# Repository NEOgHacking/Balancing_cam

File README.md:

# Balancing_cam
This is a side project to improve on the  with a new smaller esd protected pcb to prevent failures on the board, also to make the board smaller and make room for a second battery pack.
# PCB

This is a small 50x50 PCB made in kicad, it uses the esp32s3 and tmc2209 stepper drivers.
# Specs
Using:
ESP32S3 mini 1
2x TMC2209 stepper drivers
LSM6DS3 IMU
2x battery pack of 2x 18650 cells so in total 4x 18650 cells
connectivity for rc reciever and VTX

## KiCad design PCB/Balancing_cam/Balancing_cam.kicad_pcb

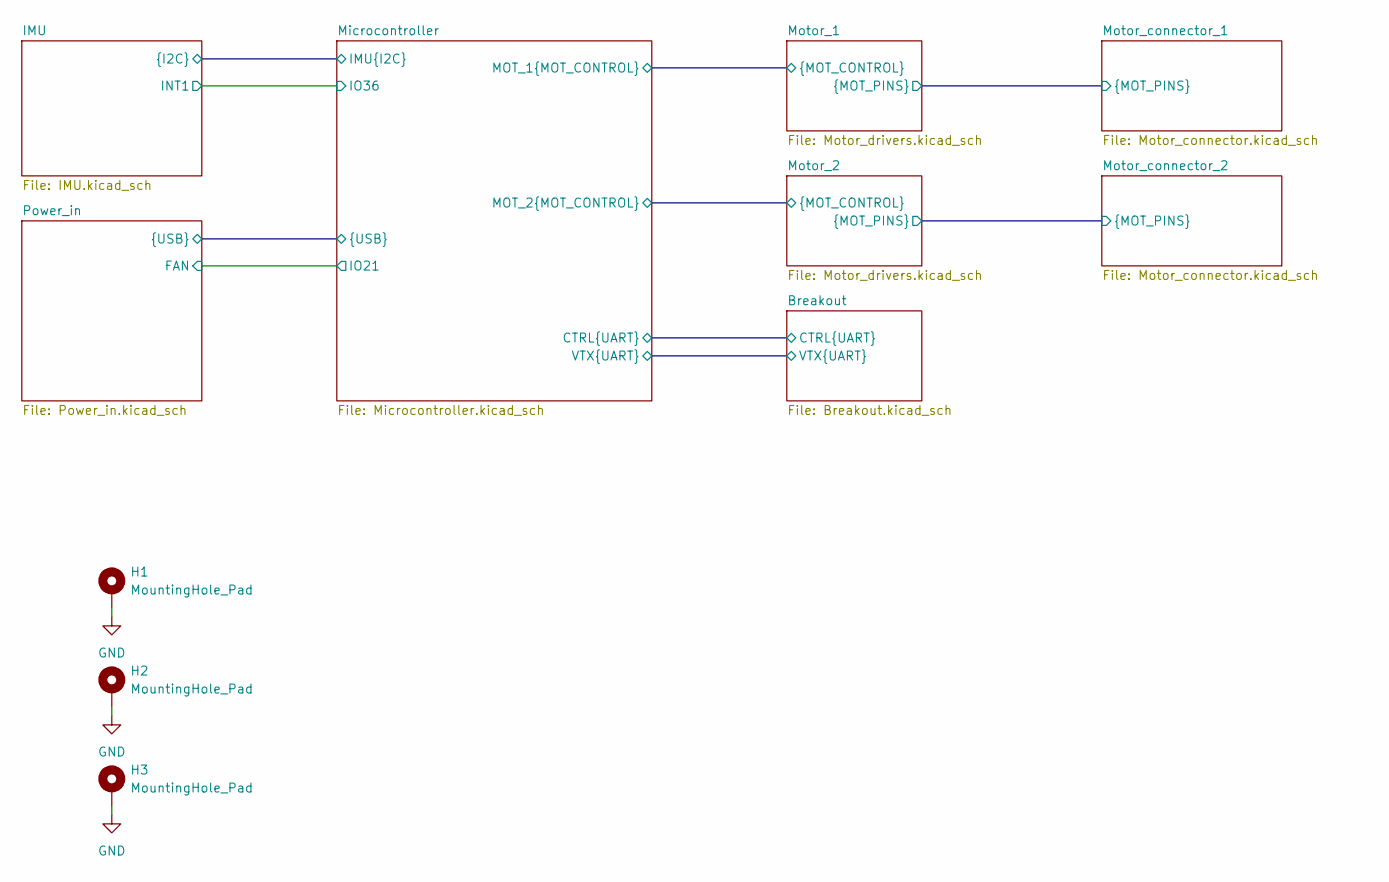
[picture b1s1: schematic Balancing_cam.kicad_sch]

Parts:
H1, H2, H3: MountingHole_Pad; MountingHole_3.2mm_M3_Pad

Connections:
GND: H1.1 (1_1), H2.1 (1_1), H3.1 (1_1); also elsewhere on the board

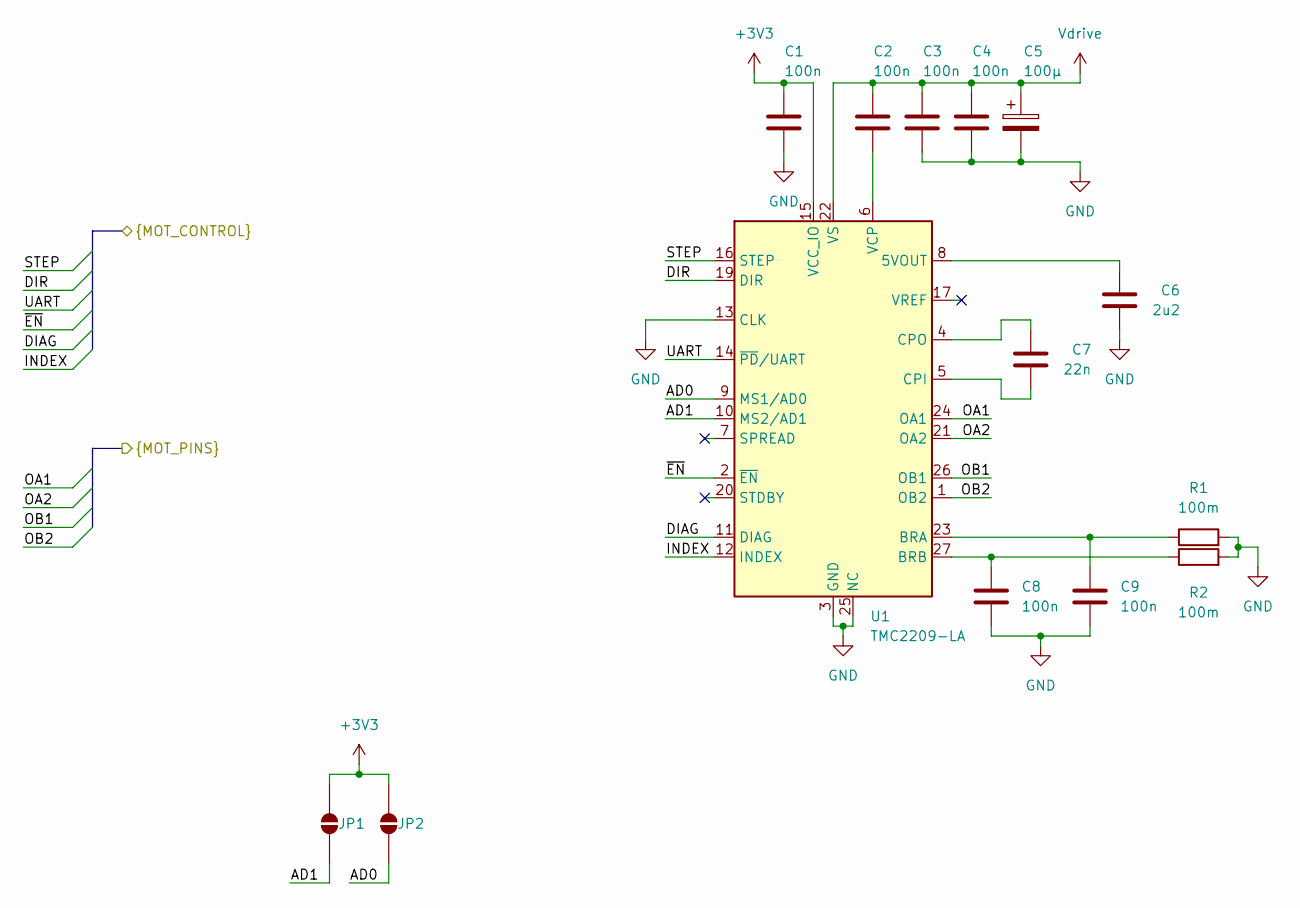
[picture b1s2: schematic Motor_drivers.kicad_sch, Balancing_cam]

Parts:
C1, C2, C3, C4, C8, C9: 100n; C_0402_1005Metric; LCSC# C307331
C5: 100μ; CP_Elec_6.3x5.4; LCSC# C2887272
C6: 2u2; C_0603_1608Metric; LCSC# C57895
C7: 22n; C_0402_1005Metric; LCSC# C337699
JP1, JP2: SolderJumper_2_Open; SolderJumper-2_P1.3mm_Open_RoundedPad1.0x1.5mm
R1, R2: 100m; R_1206_3216Metric; LCSC# C309528
U1: TMC2209-LA; VQFN-28-1EP_5x5mm_P0.5mm_EP3.7x3.7mm_ThermalVias; LCSC# C2150710

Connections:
+3V3: C1.2, JP1.1 (A), JP2.1 (A), U1.15 (VCC_IO); also elsewhere on the board
/Microcontroller/MOT_1.DIAG: U1.11 (DIAG); also elsewhere on the board
/Microcontroller/MOT_1.DIR: U1.19 (DIR); also elsewhere on the board
/Microcontroller/MOT_1.INDEX: U1.12 (INDEX); also elsewhere on the board
/Microcontroller/MOT_1.STEP: U1.16 (STEP); also elsewhere on the board
/Microcontroller/MOT_1.UART: U1.14 (~PD/UART); also elsewhere on the board
/Microcontroller/MOT_1.~EN: U1.2 (~EN); also elsewhere on the board
/Motor_1/AD0: JP2.2 (B), U1.9 (MS1/AD0)
/Motor_1/AD1: JP1.2 (B), U1.10 (MS2/AD1)
/Motor_1/OA1: U1.24 (OA1); also elsewhere on the board
/Motor_1/OA2: U1.21 (OA2); also elsewhere on the board
/Motor_1/OB1: U1.26 (OB1); also elsewhere on the board
/Motor_1/OB2: U1.1 (OB2); also elsewhere on the board
GND: C1.1, C3.1, C4.1, C5.2, C6.1, C8.2, C9.2, R1.2, R2.2, U1.3 (GND), U1.13 (CLK), U1.18 (GND), U1.25 (NC), U1.29 (GND); also elsewhere on the board
unnamed: C6.2, U1.8 (5VOUT)
unnamed: C9.1, R1.1, U1.23 (BRA)
unnamed: C8.1, R2.1, U1.27 (BRB)
unnamed: C7.1, U1.5 (CPI)
unnamed: C7.2, U1.4 (CPO)
unnamed: C2.1, U1.6 (VCP)
Vdrive: C2.2, C3.2, C4.2, C5.1, U1.22 (VS), U1.28 (VS); also elsewhere on the board

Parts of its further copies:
C10, C11, C12, C13, C17, C18: 100n; C_0402_1005Metric; LCSC# C307331
C14: 100μ; CP_Elec_6.3x5.4; LCSC# C2887272
C15: 2u2; C_0603_1608Metric; LCSC# C57895
C16: 22n; C_0402_1005Metric; LCSC# C337699
JP3, JP4: SolderJumper_2_Open; SolderJumper-2_P1.3mm_Open_RoundedPad1.0x1.5mm
R3, R4: 100m; R_1206_3216Metric; LCSC# C309528
U2: TMC2209-LA; VQFN-28-1EP_5x5mm_P0.5mm_EP3.7x3.7mm_ThermalVias; LCSC# C2150710

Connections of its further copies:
+3V3: C10.2, JP3.1 (A), JP4.1 (A), U2.15 (VCC_IO); also elsewhere on the board
/Microcontroller/MOT_1.UART: U2.14 (~PD/UART); also elsewhere on the board
/Microcontroller/MOT_2.DIAG: U2.11 (DIAG); also elsewhere on the board
/Microcontroller/MOT_2.DIR: U2.19 (DIR); also elsewhere on the board
/Microcontroller/MOT_2.INDEX: U2.12 (INDEX); also elsewhere on the board
/Microcontroller/MOT_2.STEP: U2.16 (STEP); also elsewhere on the board
/Microcontroller/MOT_2.~EN: U2.2 (~EN); also elsewhere on the board
/Motor_2/AD0: JP4.2 (B), U2.9 (MS1/AD0)
/Motor_2/AD1: JP3.2 (B), U2.10 (MS2/AD1)
/Motor_2/OA1: U2.24 (OA1); also elsewhere on the board
/Motor_2/OA2: U2.21 (OA2); also elsewhere on the board
/Motor_2/OB1: U2.26 (OB1); also elsewhere on the board
/Motor_2/OB2: U2.1 (OB2); also elsewhere on the board
GND: C10.1, C12.1, C13.1, C14.2, C15.1, C17.2, C18.2, R3.2, R4.2, U2.3 (GND), U2.13 (CLK), U2.18 (GND), U2.25 (NC), U2.29 (GND); also elsewhere on the board
unnamed: C15.2, U2.8 (5VOUT)
unnamed: C18.1, R3.1, U2.23 (BRA)
unnamed: C17.1, R4.1, U2.27 (BRB)
unnamed: C16.1, U2.5 (CPI)
unnamed: C16.2, U2.4 (CPO)
unnamed: C11.1, U2.6 (VCP)
Vdrive: C11.2, C12.2, C13.2, C14.1, U2.22 (VS), U2.28 (VS); also elsewhere on the board

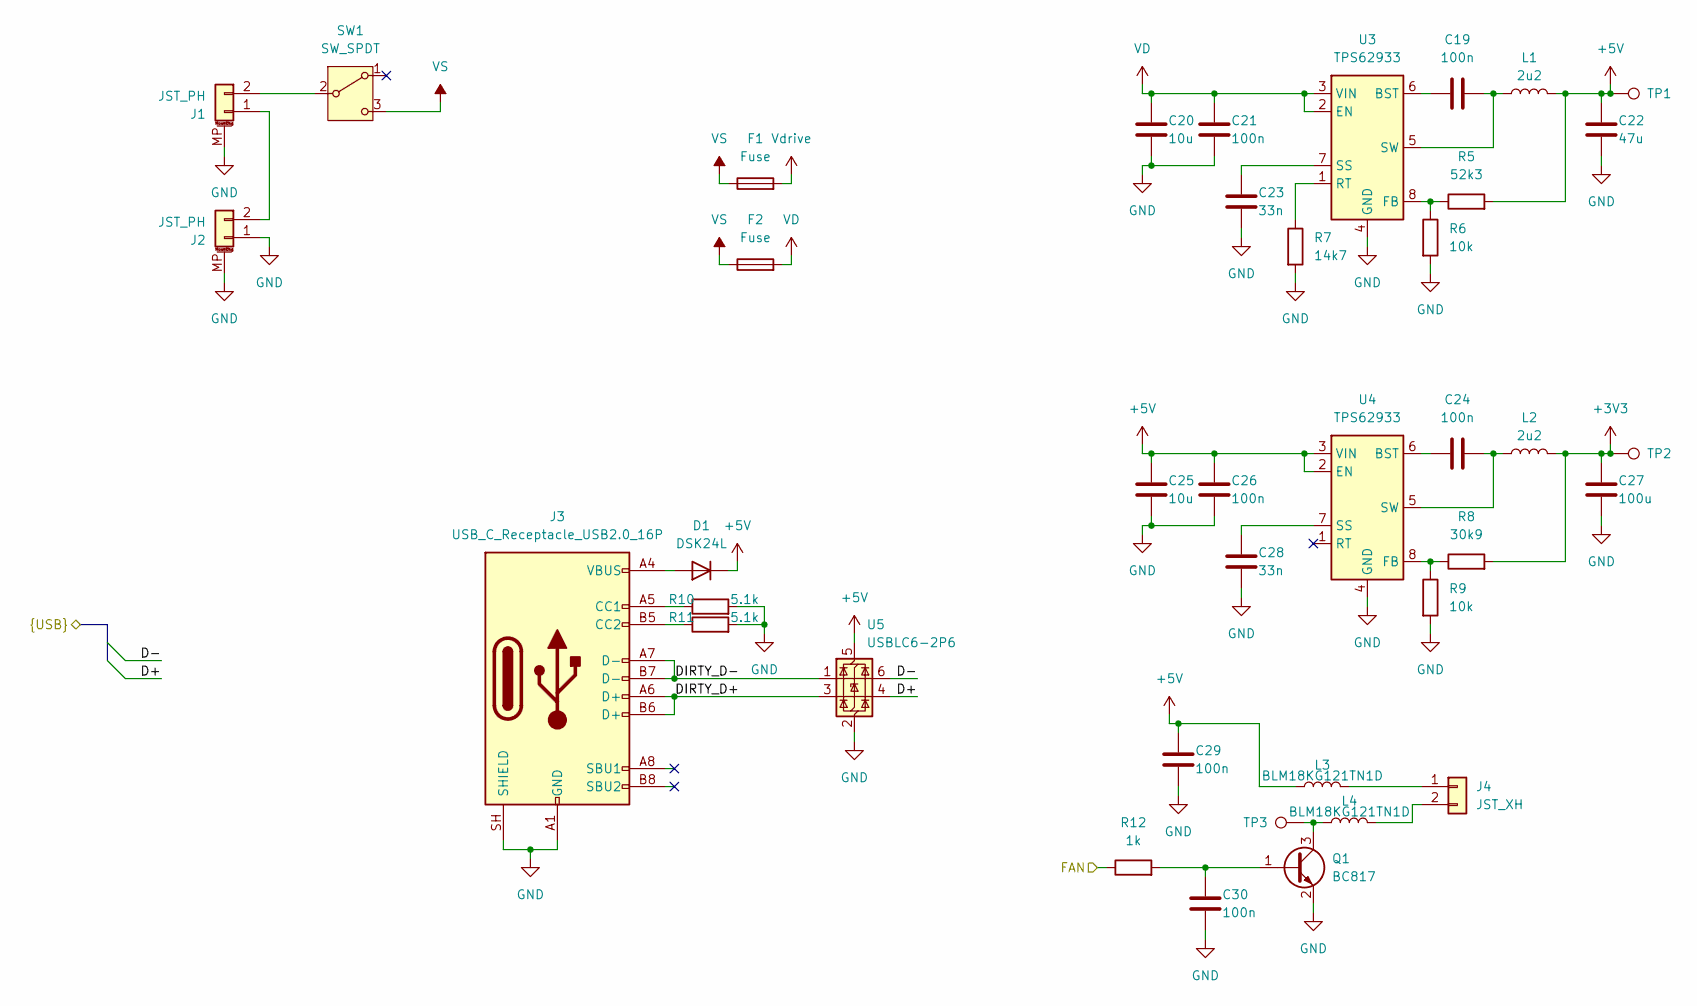
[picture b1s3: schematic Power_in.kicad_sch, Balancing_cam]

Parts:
C19, C21, C24, C26, C29, C30: 100n; C_0402_1005Metric; LCSC# C307331
C20, C25: 10u; C_0603_1608Metric; LCSC# C194427
C22: 47u; C_0805_2012Metric; LCSC# C19103846
C23, C28: 33n; C_0402_1005Metric; LCSC# C472437
C27: 100u; C_1206_3216Metric; LCSC# C380356
D1: DSK24L; D_SOD-123F; LCSC# C2939005
F1, F2: Fuse; Fuseholder_Littelfuse_Nano2_154x; LCSC# C108518
J1, J2: JST_PH; JST_PH_S2B-PH-SM4-TB_1x02-1MP_P2.00mm_Horizontal; LCSC# C295747
J3: USB_C_Receptacle_USB2.0_16P; USB_C_Receptacle_GCT_USB4105-xx-A_16P_TopMnt_Horizontal; LCSC# C165948
J4: JST_XH; JST_XH_B2B-XH-A_1x02_P2.50mm_Vertical; LCSC# C158012
L1, L2: 2u2; L_1210_3225Metric; LCSC# C3222669
L3, L4: BLM18KG121TN1D; L_0603_1608Metric; LCSC# C85831
Q1: BC817; SOT-23; LCSC# C52801
R5: 52k3; R_0402_1005Metric; LCSC# C2998086
R6, R9: 10k; R_0402_1005Metric; LCSC# C2906861
R7: 14k7; R_0402_1005Metric; LCSC# C2929988
R8: 30k9; R_0402_1005Metric; LCSC# C2933086
R10, R11: 5.1k; R_0603_1608Metric; LCSC# C105580
R12: 1k; R_0402_1005Metric; LCSC# C2906864
SW1: SW_SPDT; SS12D10G5; LCSC# C7431054
TP1, TP2, TP3: TestPoint; TestPoint_Pad_D1.5mm
U3, U4: TPS62933; SOT-583-8; LCSC# C3200405
U5: USBLC6-2P6; SOT-666; LCSC# C15999

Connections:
+3V3: C27.1, L2.2, R8.2, TP2.1 (1_1); also elsewhere on the board
+5V: C22.1, C25.1, C26.1, C29.1, D1.1 (K), L1.2, L3.1, R5.2, TP1.1 (1_1), U4.2 (EN), U4.3 (VIN), U5.5 (VBUS); also elsewhere on the board
/Microcontroller/D+: U5.4 (I/O2); also elsewhere on the board
/Microcontroller/D-: U5.6 (I/O1); also elsewhere on the board
/Microcontroller/IO21: R12.1; also elsewhere on the board
/Power_in/DIRTY_D+: J3.A6 (D+), J3.B6 (D+), U5.3 (I/O2)
/Power_in/DIRTY_D-: J3.A7 (D-), J3.B7 (D-), U5.1 (I/O1)
GND: C20.2, C21.2, C22.2, C23.2, C25.2, C26.2, C27.2, C28.2, C29.2, C30.2, J1.MP (MountPin), J2.1 (Pin_2), J2.MP (MountPin), J3.A1 (GND), J3.A12 (GND), J3.B1 (GND), J3.B12 (GND), J3.SH (SHIELD), Q1.2 (E), R6.2, R7.2, R9.2, R10.2, R11.2, U3.4 (GND), U4.4 (GND), U5.2 (GND); also elsewhere on the board
unnamed: D1.2 (A), J3.A4 (VBUS), J3.A9 (VBUS), J3.B4 (VBUS), J3.B9 (VBUS)
unnamed: J1.2 (Pin_1), SW1.2 (B)
unnamed: J1.1 (Pin_2), J2.2 (Pin_1)
unnamed: J3.A5 (CC1), R10.1
unnamed: J3.B5 (CC2), R11.1
unnamed: J4.1, L3.2
unnamed: J4.2, L4.2
unnamed: C30.1, Q1.1 (B), R12.2
unnamed: L4.1, Q1.3 (C), TP3.1 (1_1)
unnamed: C19.1, U3.6 (BST)
unnamed: R5.1, R6.1, U3.8 (FB)
unnamed: R7.1, U3.1 (RT)
unnamed: C23.1, U3.7 (SS)
unnamed: C19.2, L1.1, U3.5 (SW)
unnamed: C24.1, U4.6 (BST)
unnamed: R8.1, R9.1, U4.8 (FB)
unnamed: C28.1, U4.7 (SS)
unnamed: C24.2, L2.1, U4.5 (SW)
VD: C20.1, C21.1, F2.2, U3.2 (EN), U3.3 (VIN)
VS: F1.1, F2.1, SW1.3 (C)
Vdrive: F1.2; also elsewhere on the board

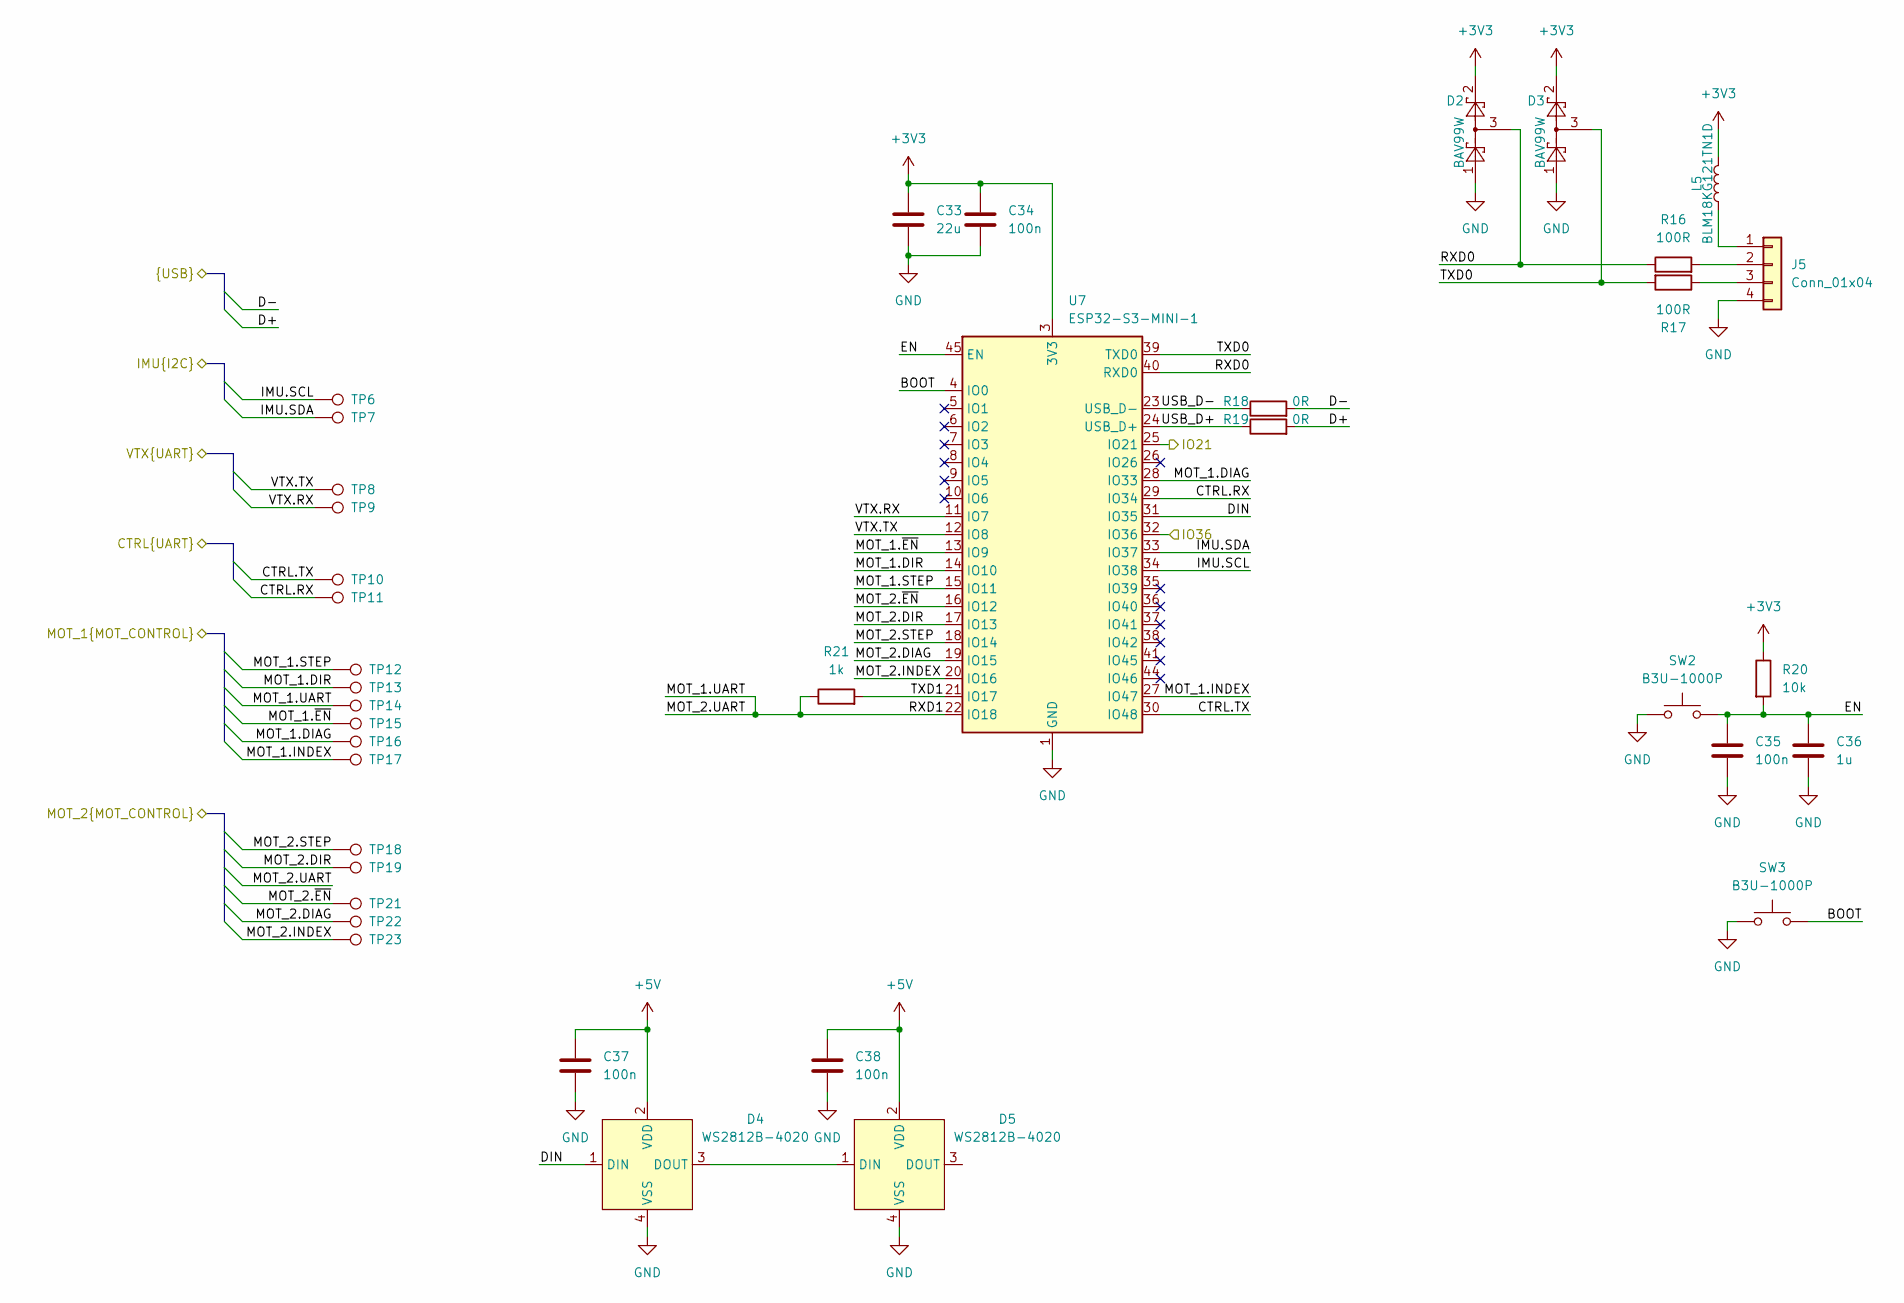
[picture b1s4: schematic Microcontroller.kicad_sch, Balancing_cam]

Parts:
C33: 22u; C_0603_1608Metric; LCSC# C59461
C34, C35, C37, C38: 100n; C_0402_1005Metric; LCSC# C307331
C36: 1u; C_0402_1005Metric; LCSC# C14445
D2, D3: BAV99W; SOT-23; LCSC# C7502727
D4, D5: WS2812B-4020; LCSC# C965557
J5: Conn_01x04; PinHeader_1x04_P2.54mm_Vertical; LCSC# C7501262
L5: BLM18KG121TN1D; L_0603_1608Metric; LCSC# C85831
R16, R17: 100R; R_0603_1608Metric; LCSC# C105588
R18, R19: 0R; R_0402_1005Metric; LCSC# C2906858
R20: 10k; R_0402_1005Metric; LCSC# C2906861
R21: 1k; R_0402_1005Metric; LCSC# C2906864
SW2, SW3: B3U-1000P; SW_SPST_B3U-1000P; LCSC# C231329
TP6, TP7, TP8, TP9, TP10, TP11, TP12, TP13, TP14, TP15, TP16, TP17, TP18, TP19, TP21, TP22, TP23: TestPoint; TestPoint_Pad_D1.5mm
U7: ESP32-S3-MINI-1; ESP32-S2-MINI-1; LCSC# C2913206

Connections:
+3V3: C33.1, C34.1, D2.2, D3.2, L5.2, R20.1, U7.3 (3V3); also elsewhere on the board
+5V: C37.1, C38.1, D4.2 (VDD), D5.2 (VDD); also elsewhere on the board
/Breakout/CTRL.RX: TP11.1 (1_1), U7.29 (IO34); also elsewhere on the board
/Breakout/CTRL.TX: TP10.1 (1_1), U7.30 (IO48); also elsewhere on the board
/Breakout/VTX.RX: TP9.1 (1_1), U7.11 (IO7); also elsewhere on the board
/Breakout/VTX.TX: TP8.1 (1_1), U7.12 (IO8); also elsewhere on the board
/IMU/INT1: U7.32 (IO36); also elsewhere on the board
/IMU/SCL: TP6.1 (1_1), U7.34 (IO38); also elsewhere on the board
/IMU/SDA: TP7.1 (1_1), U7.33 (IO37); also elsewhere on the board
/Microcontroller/BOOT: SW3.2, U7.4 (IO0)
/Microcontroller/D+: R19.2; also elsewhere on the board
/Microcontroller/D-: R18.2; also elsewhere on the board
/Microcontroller/DIN: D4.1 (DIN), U7.31 (IO35)
/Microcontroller/EN: C35.1, C36.1, R20.2, SW2.2, U7.45 (EN)
/Microcontroller/IO21: U7.25 (IO21); also elsewhere on the board
/Microcontroller/MOT_1.DIAG: TP16.1 (1_1), U7.28 (IO33); also elsewhere on the board
/Microcontroller/MOT_1.DIR: TP13.1 (1_1), U7.14 (IO10); also elsewhere on the board
/Microcontroller/MOT_1.INDEX: TP17.1 (1_1), U7.27 (IO47); also elsewhere on the board
/Microcontroller/MOT_1.STEP: TP12.1 (1_1), U7.15 (IO11); also elsewhere on the board
/Microcontroller/MOT_1.UART: R21.1, TP14.1 (1_1), U7.22 (IO18); also elsewhere on the board
/Microcontroller/MOT_1.~EN: TP15.1 (1_1), U7.13 (IO9); also elsewhere on the board
/Microcontroller/MOT_2.DIAG: TP22.1 (1_1), U7.19 (IO15); also elsewhere on the board
/Microcontroller/MOT_2.DIR: TP19.1 (1_1), U7.17 (IO13); also elsewhere on the board
/Microcontroller/MOT_2.INDEX: TP23.1 (1_1), U7.20 (IO16); also elsewhere on the board
/Microcontroller/MOT_2.STEP: TP18.1 (1_1), U7.18 (IO14); also elsewhere on the board
/Microcontroller/MOT_2.~EN: TP21.1 (1_1), U7.16 (IO12); also elsewhere on the board
/Microcontroller/RXD0: D2.3, R16.1, U7.40 (RXD0)
/Microcontroller/TXD0: D3.3, R17.2, U7.39 (TXD0)
/Microcontroller/TXD1: R21.2, U7.21 (IO17)
/Microcontroller/USB_D+: R19.1, U7.24 (USB_D+)
/Microcontroller/USB_D-: R18.1, U7.23 (USB_D-)
GND: C33.2, C34.2, C35.2, C36.2, C37.2, C38.2, D2.1, D3.1, D4.4 (VSS), D5.4 (VSS), J5.4, SW2.1, SW3.1, U7.1 (GND), U7.2 (GND), U7.42 (GND), U7.43 (GND), U7.46 (GND), U7.47 (GND), U7.48 (GND), U7.49 (GND), U7.50 (GND), U7.51 (GND), U7.52 (GND), U7.53 (GND), U7.54 (GND), U7.55 (GND), U7.56 (GND), U7.57 (GND), U7.58 (GND), U7.59 (GND), U7.60 (GND), U7.61 (GND), U7.62 (GND), U7.63 (GND), U7.64 (GND), U7.65 (GND); also elsewhere on the board
unnamed: D4.3 (DOUT), D5.1 (DIN)
unnamed: J5.1, L5.1
unnamed: J5.2, R16.2
unnamed: J5.3, R17.1

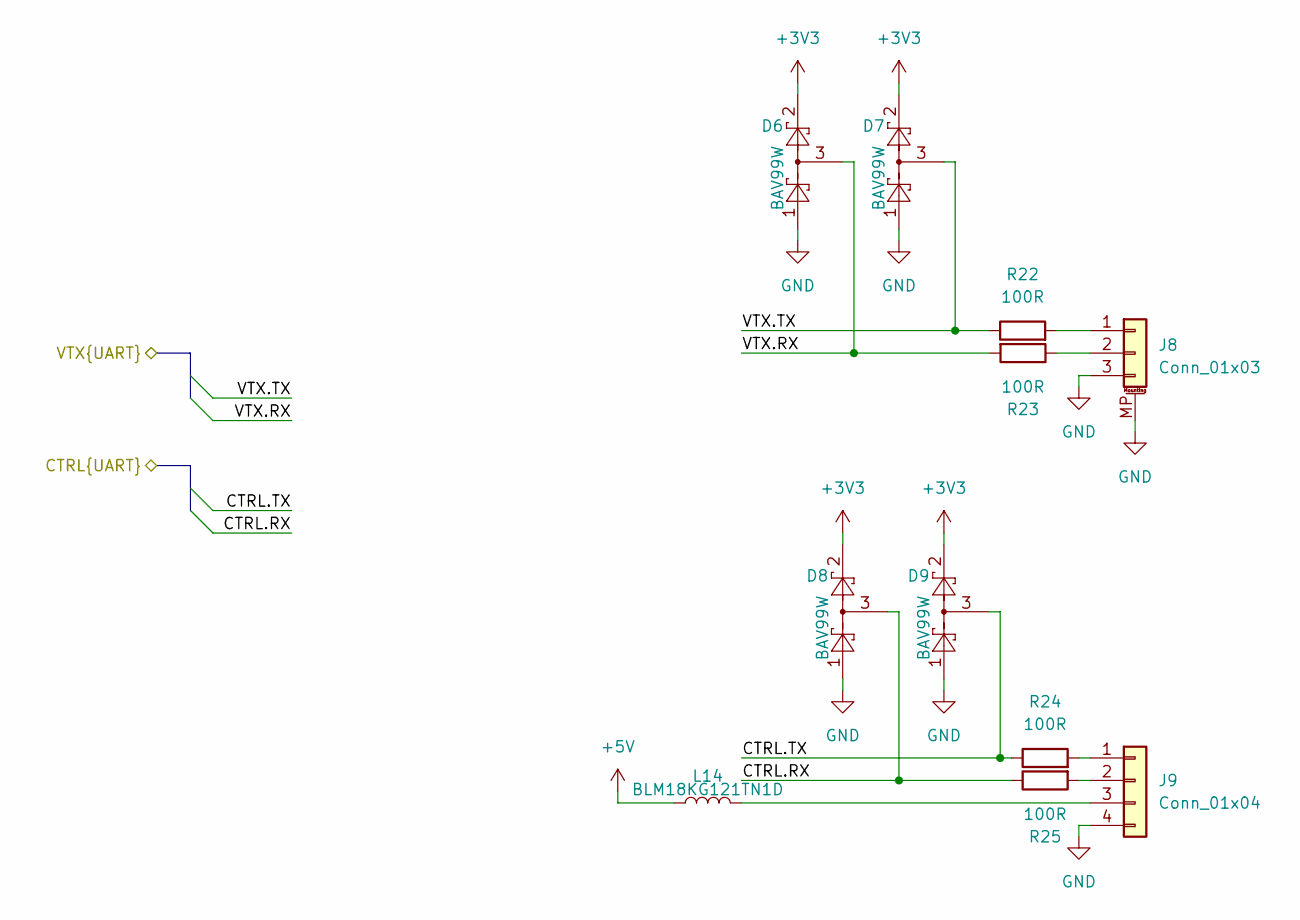
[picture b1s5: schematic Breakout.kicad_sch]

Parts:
D6, D7, D8, D9: BAV99W; SOT-23; LCSC# C7502727
J8: Conn_01x03; JST_GH_BM03B-GHS-TBT_1x03-1MP_P1.25mm_Vertical; LCSC# C160389
J9: Conn_01x04; PinHeader_1x04_P2.54mm_Vertical; LCSC# C7501262
L14: BLM18KG121TN1D; L_0603_1608Metric; LCSC# C85831
R22, R23, R24, R25: 100R; R_0603_1608Metric; LCSC# C105588

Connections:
+3V3: D6.2, D7.2, D8.2, D9.2; also elsewhere on the board
+5V: L14.1; also elsewhere on the board
/Breakout/CTRL.RX: D8.3, R25.1; also elsewhere on the board
/Breakout/CTRL.TX: D9.3, R24.1; also elsewhere on the board
/Breakout/VTX.RX: D6.3, R23.2; also elsewhere on the board
/Breakout/VTX.TX: D7.3, R22.1; also elsewhere on the board
GND: D6.1, D7.1, D8.1, D9.1, J8.3, J8.MP (MountPin), J9.4; also elsewhere on the board
unnamed: J8.1, R22.2
unnamed: J8.2, R23.1
unnamed: J9.1, R24.2
unnamed: J9.2, R25.2
unnamed: J9.3, L14.2

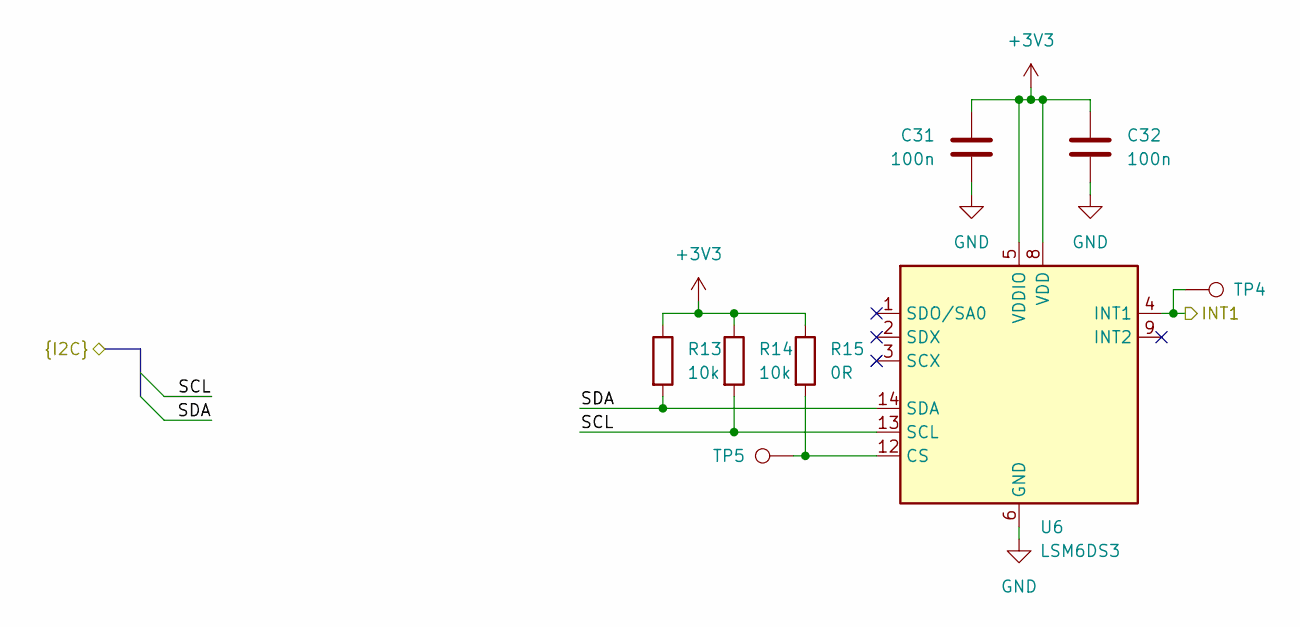
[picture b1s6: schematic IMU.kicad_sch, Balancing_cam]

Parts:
C31, C32: 100n; C_0402_1005Metric; LCSC# C307331
R13, R14: 10k; R_0402_1005Metric; LCSC# C2906861
R15: 0R; R_0402_1005Metric; LCSC# C2906858
TP4, TP5: TestPoint; TestPoint_Pad_D1.5mm
U6: LSM6DS3; LGA-14_3x2.5mm_P0.5mm_LayoutBorder3x4y; LCSC# C967633

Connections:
+3V3: C31.1, C32.1, R13.1, R14.1, R15.1, U6.5 (VDDIO), U6.8 (VDD); also elsewhere on the board
/IMU/INT1: TP4.1 (1_1), U6.4 (INT1); also elsewhere on the board
/IMU/SCL: R14.2, U6.13 (SCL); also elsewhere on the board
/IMU/SDA: R13.2, U6.14 (SDA); also elsewhere on the board
GND: C31.2, C32.2, U6.6 (GND), U6.7 (GND); also elsewhere on the board
unnamed: R15.2, TP5.1 (1_1), U6.12 (CS)

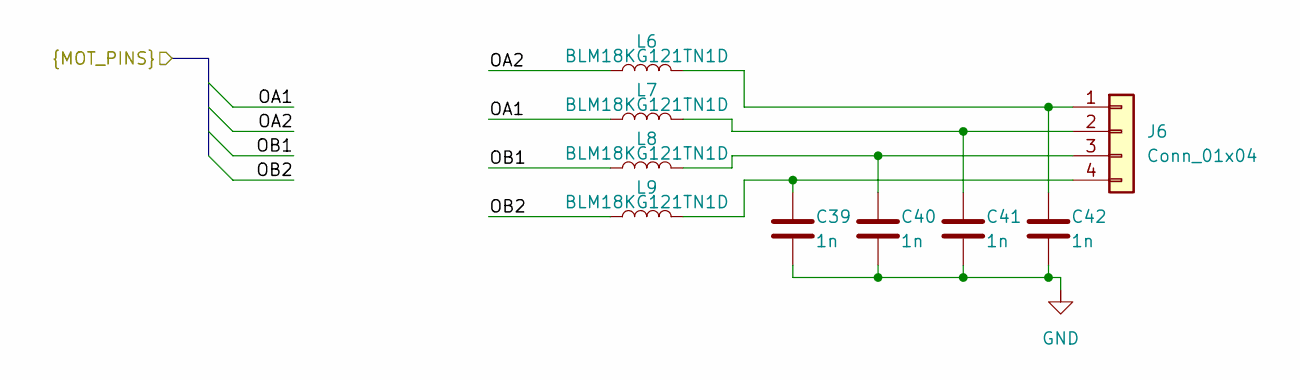
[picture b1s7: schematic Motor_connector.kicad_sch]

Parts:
C39, C40, C41, C42: 1n; C_0603_1608Metric; LCSC# C153291
J6: Conn_01x04; JST_XH_B4B-XH-A_1x04_P2.50mm_Vertical; LCSC# C144395
L6, L7, L8, L9: BLM18KG121TN1D; L_0603_1608Metric; LCSC# C85831

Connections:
/Motor_1/OA1: L7.1; also elsewhere on the board
/Motor_1/OA2: L6.1; also elsewhere on the board
/Motor_1/OB1: L8.1; also elsewhere on the board
/Motor_1/OB2: L9.1; also elsewhere on the board
GND: C39.2, C40.2, C41.2, C42.2; also elsewhere on the board
unnamed: C42.1, J6.1, L6.2
unnamed: C41.1, J6.2, L7.2
unnamed: C40.1, J6.3, L8.2
unnamed: C39.1, J6.4, L9.2

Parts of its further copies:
C43, C44, C45, C46: 1n; C_0603_1608Metric; LCSC# C153291
J7: Conn_01x04; JST_XH_B4B-XH-A_1x04_P2.50mm_Vertical; LCSC# C144395
L10, L11, L12, L13: BLM18KG121TN1D; L_0603_1608Metric; LCSC# C85831

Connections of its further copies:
/Motor_2/OA1: L11.1; also elsewhere on the board
/Motor_2/OA2: L10.1; also elsewhere on the board
/Motor_2/OB1: L12.1; also elsewhere on the board
/Motor_2/OB2: L13.1; also elsewhere on the board
GND: C43.2, C44.2, C45.2, C46.2; also elsewhere on the board
unnamed: C46.1, J7.1, L10.2
unnamed: C45.1, J7.2, L11.2
unnamed: C44.1, J7.3, L12.2
unnamed: C43.1, J7.4, L13.2

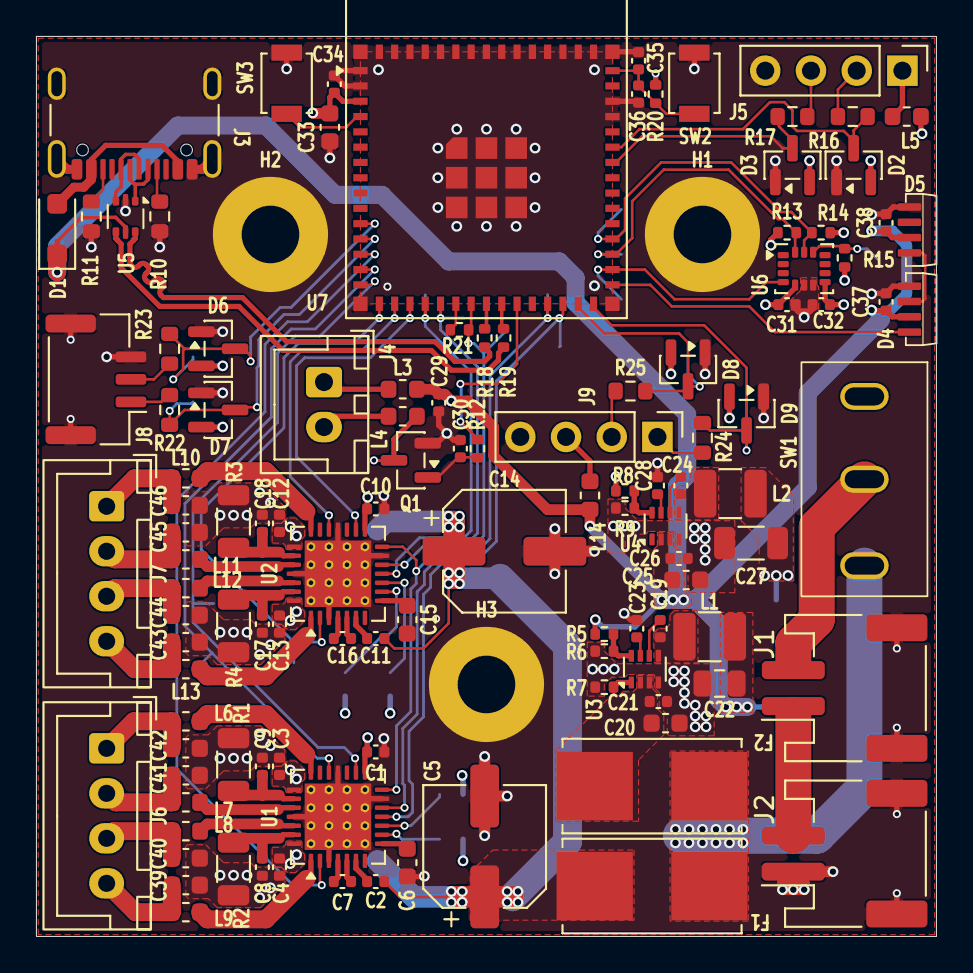
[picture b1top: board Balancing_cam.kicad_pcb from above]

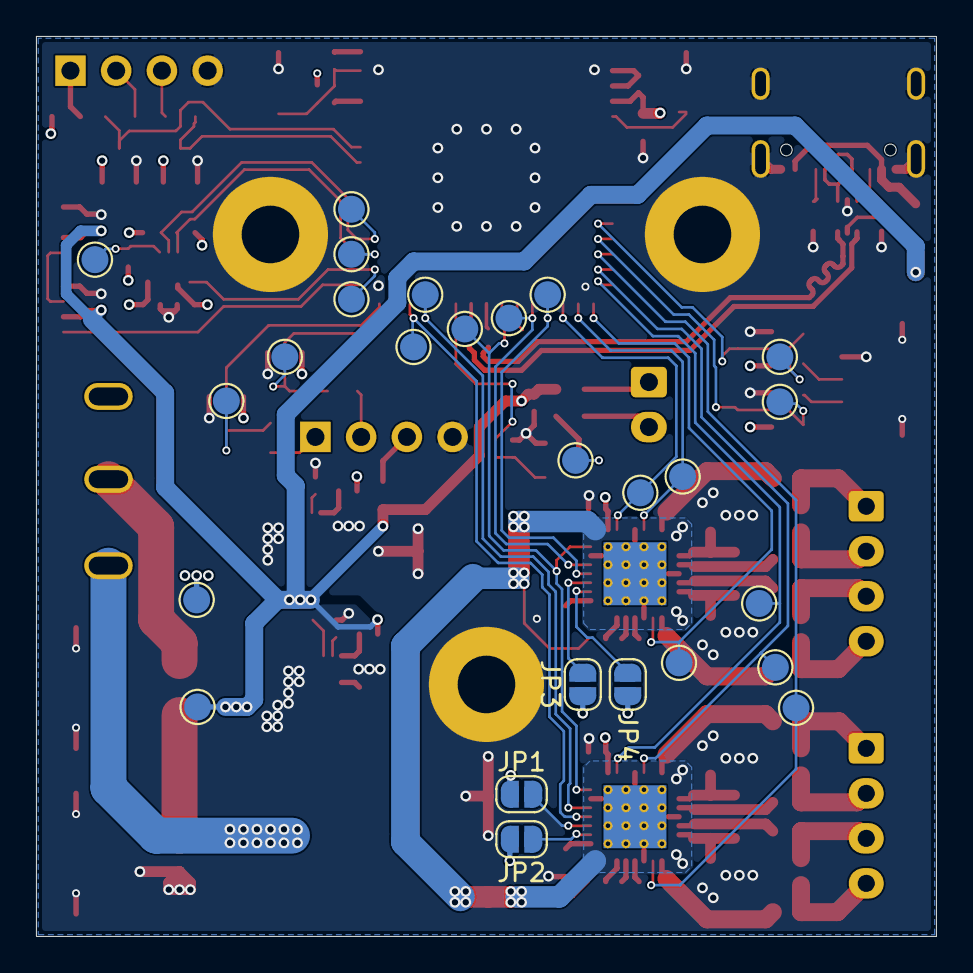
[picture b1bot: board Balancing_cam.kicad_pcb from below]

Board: 4 copper layers, 50.0 x 50.0 mm, 145 parts (26 on the bottom side), 97 nets.

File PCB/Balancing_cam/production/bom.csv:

Designator,Footprint,Quantity,Value,LCSC Part #
"C1_4, C1_3, C1_2, C1, C10_4, C10_3, C10_2, C10, C11_4, C11_3, C11_2, C11, C12_4, C12_3, C12_2, C12, C13_4, C13_3, C13_2, C13, C17_4, C17_3, C17_2, C17, C18_4, C18_3, C18_2, C18, C19_4, C19_3, C19_2, C19, C2_4, C2_3, C2_2, C2, C21_4, C21_3, C21_2, C21, C24_4, C24_3, C24_2, C24, C26_4, C26_3, C26_2, C26, C29_4, C29_3, C29_2, C29, C3_4, C3_3, C3_2, C3, C30_4, C30_3, C30_2, C30, C31_4, C31_3, C31_2, C31, C32_4, C32_3, C32_2, C32, C34_4, C34_3, C34_2, C34, C35_4, C35_3, C35_2, C35, C37_4, C37_3, C37_2, C37, C38_4, C38_3, C38_2, C38, C4_4, C4_3, C4_2, C4, C8_4, C8_3, C8_2, C8, C9_4, C9_3, C9_2, C9",0402,96,100n,
"C14_4, C14_3, C14_2, C14, C5_4, C5_3, C5_2, C5",CP_Elec_6.3x5.4,8,100μ,
"C15_4, C15_3, C15_2, C15, C6_4, C6_3, C6_2, C6",0603,8,2u2,
"C16_4, C16_3, C16_2, C16, C7_4, C7_3, C7_2, C7",0402,8,22n,
"C20_4, C20_3, C20_2, C20, C25_4, C25_3, C25_2, C25",0603,8,10u,
"C22_4, C22_3, C22_2, C22",0805,4,47u,
"C23_4, C23_3, C23_2, C23, C28_4, C28_3, C28_2, C28",0402,8,33n,
"C27_4, C27_3, C27_2, C27",1206,4,100u,
"C33_4, C33_3, C33_2, C33",0603,4,22u,
"C36_4, C36_3, C36_2, C36",0402,4,1u,
"C39_4, C39_3, C39_2, C39, C40_4, C40_3, C40_2, C40, C41_4, C41_3, C41_2, C41, C42_4, C42_3, C42_2, C42, C43_4, C43_3, C43_2, C43, C44_4, C44_3, C44_2, C44, C45_4, C45_3, C45_2, C45, C46_4, C46_3, C46_2, C46",0603,32,1n,
"D1_4, D1_3, D1_2, D1",D_SOD-123F,4,DSK24L,
"D2_4, D2_3, D2_2, D2, D3_4, D3_3, D3_2, D3, D6_4, D6_3, D6_2, D6, D7_4, D7_3, D7_2, D7, D8_4, D8_3, D8_2, D8, D9_4, D9_3, D9_2, D9",SOT-23,24,BAV99W,
"D4_4, D4_3, D4_2, D4, D5_4, D5_3, D5_2, D5",WS2812B-4020,8,WS2812B-4020,
"F1_4, F1_3, F1_2, F1, F2_4, F2_3, F2_2, F2",Fuseholder_Littelfuse_Nano2_154x,8,Fuse,
"J1_4, J1_3, J1_2, J1, J2_4, J2_3, J2_2, J2",JST_PH_S2B-PH-SM4-TB_1x02-1MP_P2.00mm_Horizontal,8,JST_PH,
"J3_4, J3_3, J3_2, J3",USB_C_Receptacle_GCT_USB4105-xx-A_16P_TopMnt_Horizontal,4,USB_C_Receptacle_USB2.0_16P,
"J4_4, J4_3, J4_2, J4",JST_XH_B2B-XH-A_1x02_P2.50mm_Vertical,4,JST_XH,
"J5_4, J5_3, J5_2, J5, J9_4, J9_3, J9_2, J9",PinHeader_1x04_P2.54mm_Vertical,8,Conn_01x04,
"J6_4, J6_3, J6_2, J6, J7_4, J7_3, J7_2, J7",JST_XH_B4B-XH-A_1x04_P2.50mm_Vertical,8,Conn_01x04,
"J8_4, J8_3, J8_2, J8",JST_GH_BM03B-GHS-TBT_1x03-1MP_P1.25mm_Vertical,4,Conn_01x03,
"L1_4, L1_3, L1_2, L1, L2_4, L2_3, L2_2, L2",1210,8,2u2,
"L10_4, L10_3, L10_2, L10, L11_4, L11_3, L11_2, L11, L12_4, L12_3, L12_2, L12, L13_4, L13_3, L13_2, L13, L14_4, L14_3, L14_2, L14, L3_4, L3_3, L3_2, L3, L4_4, L4_3, L4_2, L4, L5_4, L5_3, L5_2, L5, L6_4, L6_3, L6_2, L6, L7_4, L7_3, L7_2, L7, L8_4, L8_3, L8_2, L8, L9_4, L9_3, L9_2, L9",0603,48,BLM18KG121TN1D,
"Q1_4, Q1_3, Q1_2, Q1",SOT-23,4,BC817,
"R1_4, R1_3, R1_2, R1, R2_4, R2_3, R2_2, R2, R3_4, R3_3, R3_2, R3, R4_4, R4_3, R4_2, R4",1206,16,100m,
"R10_4, R10_3, R10_2, R10, R11_4, R11_3, R11_2, R11",0603,8,5.1k,
"R12_4, R12_3, R12_2, R12, R21_4, R21_3, R21_2, R21",0402,8,1k,
"R13_4, R13_3, R13_2, R13, R14_4, R14_3, R14_2, R14, R20_4, R20_3, R20_2, R20, R6_4, R6_3, R6_2, R6, R9_4, R9_3, R9_2, R9",0402,20,10k,
"R15_4, R15_3, R15_2, R15, R18_4, R18_3, R18_2, R18, R19_4, R19_3, R19_2, R19",0402,12,0R,
"R16_4, R16_3, R16_2, R16, R17_4, R17_3, R17_2, R17, R22_4, R22_3, R22_2, R22, R23_4, R23_3, R23_2, R23, R24_4, R24_3, R24_2, R24, R25_4, R25_3, R25_2, R25",0603,24,100R,
"R5_4, R5_3, R5_2, R5",0402,4,52k3,
"R7_4, R7_3, R7_2, R7",0402,4,14k7,
"R8_4, R8_3, R8_2, R8",0402,4,30k9,
"SW1_4, SW1_3, SW1_2, SW1",SS12D10G5,4,SW_SPDT,
"SW2_4, SW2_3, SW2_2, SW2, SW3_4, SW3_3, SW3_2, SW3",SW_SPST_B3U-1000P,8,B3U-1000P,
"TP1_4, TP1_3, TP1_2, TP1, TP10_4, TP10_3, TP10_2, TP10, TP11_4, TP11_3, TP11_2, TP11, TP12_4, TP12_3, TP12_2, TP12, TP13_4, TP13_3, TP13_2, TP13, TP14_4, TP14_3, TP14_2, TP14, TP15_4, TP15_3, TP15_2, TP15, TP16_4, TP16_3, TP16_2, TP16, TP17_4, TP17_3, TP17_2, TP17, TP18_4, TP18_3, TP18_2, TP18, TP19_4, TP19_3, TP19_2, TP19, TP2_4, TP2_3, TP2_2, TP2, TP21_4, TP21_3, TP21_2, TP21, TP22_4, TP22_3, TP22_2, TP22, TP23_4, TP23_3, TP23_2, TP23, TP3_4, TP3_3, TP3_2, TP3, TP4_4, TP4_3, TP4_2, TP4, TP5_4, TP5_3, TP5_2, TP5, TP6_4, TP6_3, TP6_2, TP6, TP7_4, TP7_3, TP7_2, TP7, TP8_4, TP8_3, TP8_2, TP8, TP9_4, TP9_3, TP9_2, TP9",TestPoint_Pad_D1.5mm,88,TestPoint,
"U1_4, U1_3, U1_2, U1, U2_4, U2_3, U2_2, U2",VQFN-28-1EP_5x5mm_P0.5mm_EP3.7x3.7mm_ThermalVias,8,TMC2209-LA,
"U3_4, U3_3, U3_2, U3, U4_4, U4_3, U4_2, U4",SOT-583-8,8,TPS62933,
"U5_4, U5_3, U5_2, U5",SOT-666,4,USBLC6-2P6,
"U6_4, U6_3, U6_2, U6",LGA-14_3x2.5mm_P0.5mm_LayoutBorder3x4y,4,LSM6DS3,
"U7_4, U7_3, U7_2, U7",ESP32-S2-MINI-1,4,ESP32-S3-MINI-1,
